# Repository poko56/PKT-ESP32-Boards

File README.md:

<h1 align="center">PKT ESP32 Boards</h1>

<p align="center">
  ชุดบอร์ด ESP32 ของ <b>POKOTEAM</b> ออกแบบด้วย KiCad 10 และสร้างจากสคริปต์ทั้งหมด
</p>

---

## บอร์ดทั้งหมด

### PKT ESP32-C3 Mini

บอร์ดไร้สายขนาดจิ๋ว 20 × 34 มม. เหมาะกับโหนด ESP-NOW, เซนเซอร์ไร้สาย และอุปกรณ์ในกล่องเล็ก
มี USB-C ในตัว ไฟเลี้ยงเป็น LDO ล้วน และมีโลโก้ PKT ด้านหลัง

- โมดูล ESP32-C3-MINI-1
- อุปกรณ์ SMD ด้านเดียว สั่ง PCBA ผ่าน JLCPCB ได้
- **สถานะ:** ไฟล์พร้อมสั่ง

[ดูรายละเอียดและวงจร](boards/c3-mini)

<br clear="right">

### ESP32 Dev Board

บอร์ดพัฒนาขนาด 29 × 54.6 มม. สำหรับเรียนรู้และทำต้นแบบบน breadboard
เสียบ USB-C แล้วอัปโหลดโค้ดได้เลย

- โมดูล ESP32-WROOM-32E
- CH340C พร้อมวงจร auto-reset
- **สถานะ:** มี Gerber

[ดูรายละเอียดและวงจร](boards/esp32-devboard)

<br clear="right">

### Robot Arm Controller

บอร์ดควบคุมแขนกล 5 แกน ขนาด 80 × 64 มม. สำหรับ SG90/MG90S ใช้ adapter 12V
แยกไฟ servo กับ logic มี E-stop และวัดกระแสได้

- PCA9685 + 74AHCT541 + TPS54560B + INA219
- พอร์ต DIO, ADC, I2C และ UART
- **สถานะ:** วงจรเสร็จ เดินลายยังไม่เสร็จ ยังสั่งผลิตไม่ได้

[ดูรายละเอียดและวงจร](boards/arm-controller)

<br clear="right">

> ยังไม่มีบอร์ดใดผ่านการทดสอบกับของจริง ตรวจด้วย ERC และ DRC ของ KiCad แล้วเท่านั้น

## โครงสร้าง repo

```text
PKT-ESP32-Boards
├── assets/                  โลโก้
└── boards/
    ├── c3-mini/             PKT ESP32-C3 Mini
    ├── esp32-devboard/      ESP32 Dev Board
    └── arm-controller/      Robot Arm Controller
```

แต่ละบอร์ดมีโครงสร้างเดียวกัน

| โฟลเดอร์ | เนื้อหา |
|---|---|
| `docs/` | ภาพวงจร ภาพบอร์ด และคำอธิบาย |
| `fab/` | Gerber, BOM, ตำแหน่งอุปกรณ์ และรายงาน ERC/DRC |
| `tools/` | สคริปต์สร้าง schematic และ PCB จาก `design.py` |

## Branch

| Branch | ใช้ทำอะไร |
|---|---|
| `main` | รวมทุกบอร์ด |
| `board/c3-mini` | งานของ ESP32-C3 Mini เท่านั้น |
| `board/esp32-devboard` | งานของ Dev Board เท่านั้น |
| `board/arm-controller` | งานของ Arm Controller เท่านั้น |

แก้บอร์ดไหนให้ทำใน branch ของบอร์ดนั้น แล้วค่อย merge เข้า `main`

## วิธีเปิดและสั่งผลิต

เปิดไฟล์ `.kicad_pro` ของบอร์ดใน KiCad 10

สั่ง C3 Mini ผ่าน JLCPCB ตามขั้นตอนใน [HOW_TO_ORDER.txt](boards/c3-mini/fab/HOW_TO_ORDER.txt)

แก้แบบจาก `tools/design.py` แล้วรัน `tools/build.sh` ในบอร์ดที่มีสคริปต์นี้ สคริปต์ใช้ KiCad บน macOS ที่ `/Applications/KiCad`

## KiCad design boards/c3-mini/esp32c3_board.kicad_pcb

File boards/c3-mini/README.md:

<h1 align="center">PKT ESP32-C3 Mini</h1>

<p align="center">บอร์ด ESP32-C3 ขนาด 20 × 34 มม. เน้นเล็ก ไฟสะอาด และสั่ง PCBA ผ่าน JLCPCB ได้</p>

## บอร์ดนี้คืออะไร

PKT ESP32-C3 Mini คือบอร์ดไร้สายขนาดจิ๋วที่มี USB-C ในตัว เสียบแล้วเขียนโปรแกรมได้เลย
ออกแบบมาสำหรับงานที่พื้นที่น้อยและต้องการการสื่อสารไร้สาย เช่น ESP-NOW, Wi-Fi และ Bluetooth LE

## เหมาะกับงานแบบไหน

- โหนดเซนเซอร์ไร้สาย
- อุปกรณ์สวมใส่หรืออุปกรณ์ในกล่องขนาดเล็ก
- รีโมตและตัวรับส่งข้อมูลระหว่างอุปกรณ์

## จุดเด่น

| หัวข้อ | รายละเอียด |
|---|---|
| USB | USB ในตัวชิป ไม่ต้องมีชิป USB-UART |
| ไฟเลี้ยง | LDO AP2112K-3.3 ไม่มีวงจรสวิตชิงบนบอร์ด |
| กรองไฟ | ferrite ที่ไฟเข้า และ C กรองไฟหลายค่า |
| ป้องกัน | USBLC6 กัน ESD และ B5819W กันไฟย้อน |
| เสาอากาศ | ไม่มีทองแดงในเขตเสาอากาศ |
| การประกอบ | อุปกรณ์ SMD อยู่ด้านเดียว |

## สเปก

| รายการ | ค่า |
|---|---|
| ขนาด | 20 × 34 มม. PCB 2 ชั้น |
| โมดูล | ESP32-C3-MINI-1 |
| ไฟเข้า | USB-C หรือขา 5V |
| ขา I/O | header 7 ขา 2 แถว ห่างกัน 15.24 มม. |
| GPIO | 0-7, 10, TX, RX |
| ปุ่มและไฟ | RST, BOOT, LED ที่ IO8 |

## วงจร

ดูแบบซูมได้ที่ [schematic.pdf](docs/schematic.pdf)

## สั่งผลิต

ไฟล์อยู่ใน [`fab/`](fab) และดูขั้นตอนได้ที่ [HOW_TO_ORDER.txt](fab/HOW_TO_ORDER.txt)

> สถานะ: DRC ไม่มี error และ ERC ผ่าน แต่ยังไม่ได้ทดสอบกับบอร์ดจริง
> รหัสอะไหล่บางตัวต้องยืนยันในหน้าจับคู่ของ JLCPCB ก่อนสั่ง

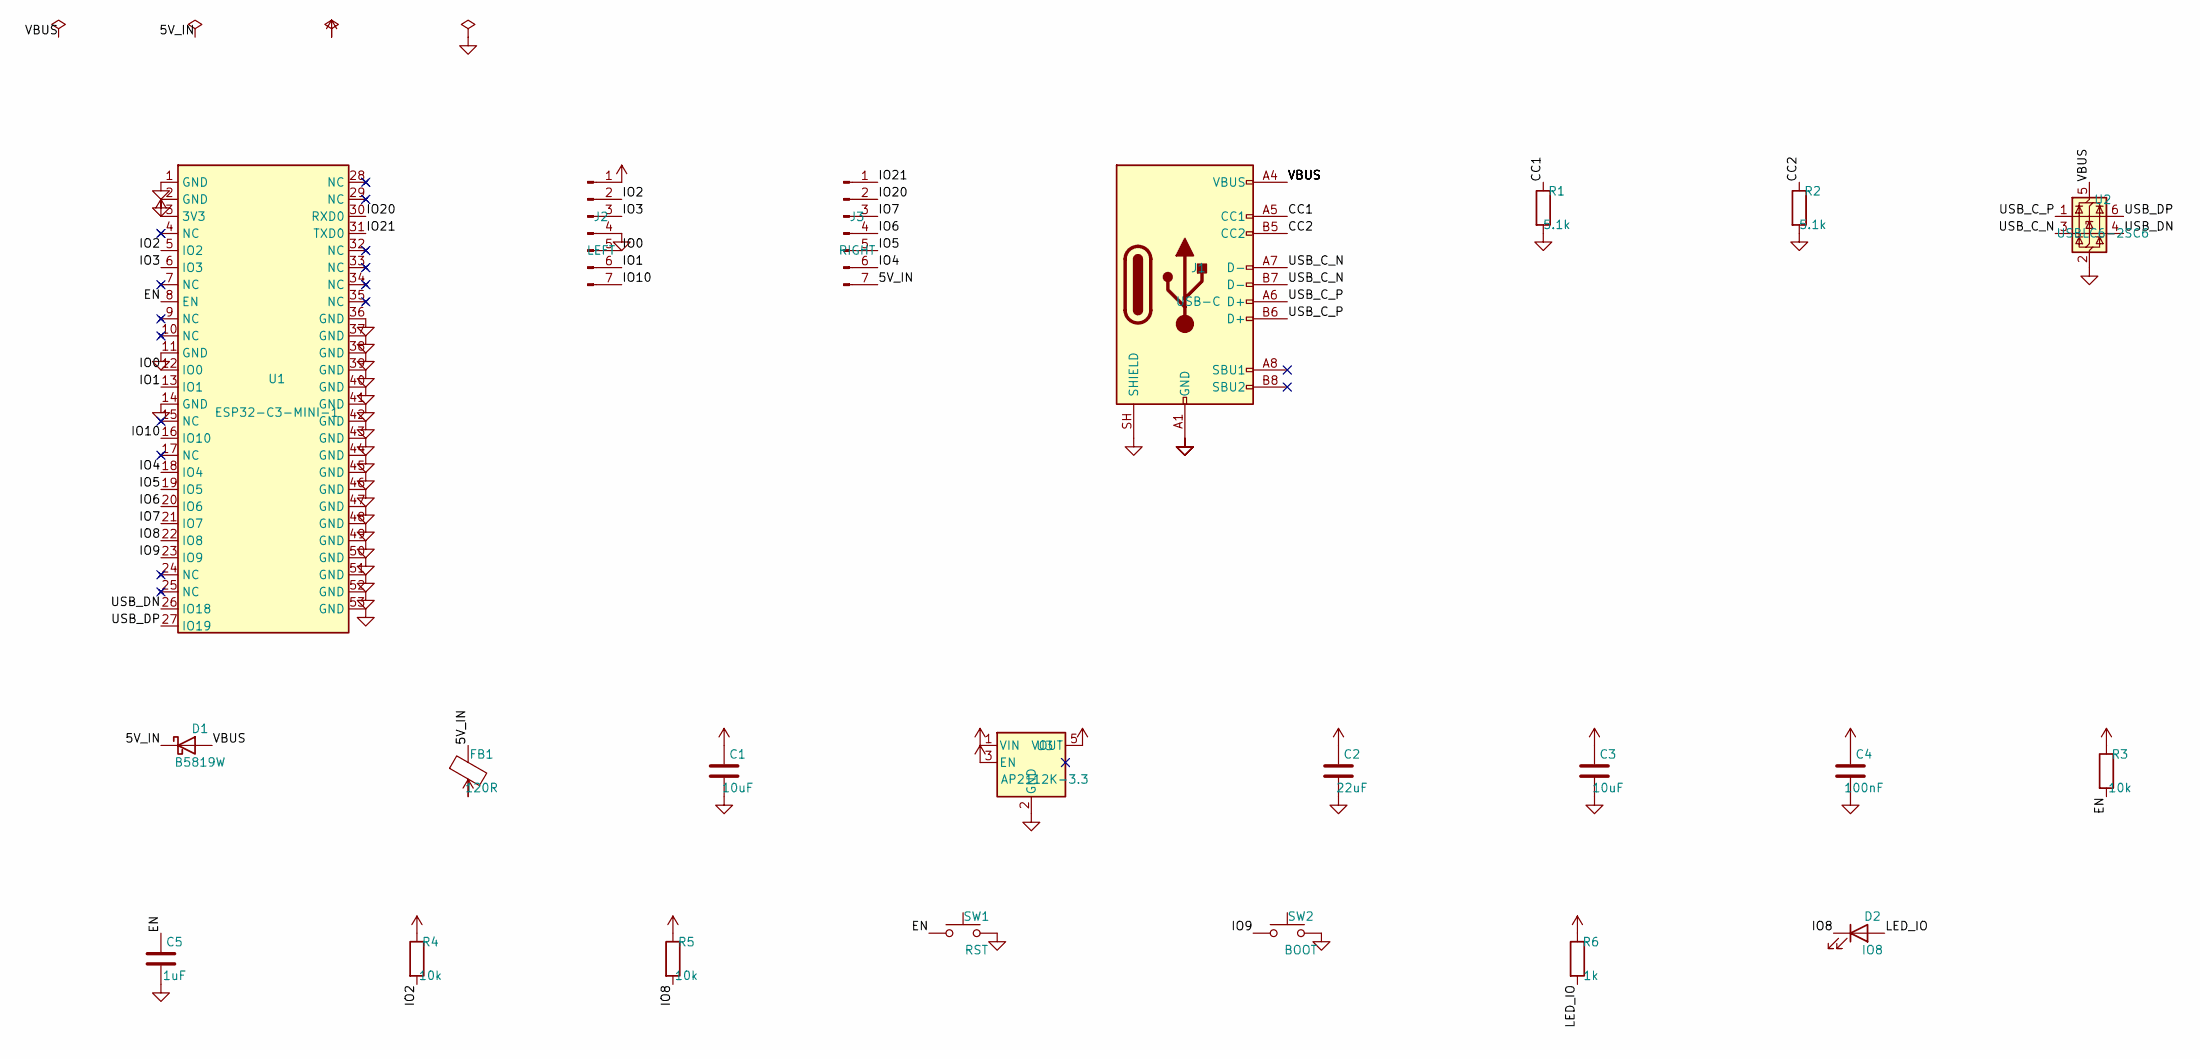
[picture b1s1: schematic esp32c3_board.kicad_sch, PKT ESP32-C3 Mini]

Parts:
C1, C3: 10uF; C_0603_1608Metric; MPN 10uF X5R/X7R 0603
C2: 22uF; C_0805_2012Metric; MPN 22uF X5R/X7R 0805
C4: 100nF; C_0402_1005Metric; MPN 100nF X5R/X7R 0402
C5: 1uF; C_0402_1005Metric; MPN 1uF X5R/X7R 0402
D1: B5819W; D_SOD-123; MPN B5819W
D2: IO8; LED_0603_1608Metric; MPN LED 0603 blue
FB1: 120R; L_0603_1608Metric; MPN 120R@100MHz >=1A 0603
J1: USB-C; USB_C_Receptacle_HRO_TYPE-C-31-M-12; MPN HRO TYPE-C-31-M-12
J2: LEFT; PinHeader_1x07_P2.54mm_Vertical; MPN 2.54mm 1x7 header (not assembled)
J3: RIGHT; PinHeader_1x07_P2.54mm_Vertical; MPN 2.54mm 1x7 header (not assembled)
R1, R2: 5.1k; R_0402_1005Metric; MPN 5.1k 1% 0402
R3, R4, R5: 10k; R_0402_1005Metric; MPN 10k 1% 0402
R6: 1k; R_0402_1005Metric; MPN 1k 1% 0402
SW1: RST; SW_Push_1P1T_NO_CK_KMR2; MPN SMD tact 4.2x2.8mm
SW2: BOOT; SW_Push_1P1T_NO_CK_KMR2; MPN SMD tact 4.2x2.8mm
U1: ESP32-C3-MINI-1; ESP32-C6-MINI-1; MPN ESP32-C3-MINI-1-N4
U2: USBLC6-2SC6; SOT-23-6; MPN USBLC6-2SC6
U3: AP2112K-3.3; SOT-23-5; MPN AP2112K-3.3TRG1

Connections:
+3V3: C2.1, C3.1, C4.1, J2.1, R3.1, R4.1, R5.1, R6.1, U1.3 (3V3), U3.5 (VOUT)
+5V: C1.1, FB1.2, U3.1 (VIN), U3.3 (EN)
/5V_IN: D1.1 (K), FB1.1, J3.7
/CC1: J1.A5 (CC1), R1.1
/CC2: J1.B5 (CC2), R2.1
/EN: C5.1, R3.2, SW1.1, U1.8 (EN)
/IO0: J2.5, U1.12 (IO0)
/IO1: J2.6, U1.13 (IO1)
/IO2: J2.2, R4.2, U1.5 (IO2)
/IO3: J2.3, U1.6 (IO3)
/IO4: J3.6, U1.18 (IO4)
/IO5: J3.5, U1.19 (IO5)
/IO6: J3.4, U1.20 (IO6)
/IO7: J3.3, U1.21 (IO7)
/IO8: D2.1 (K), R5.2, U1.22 (IO8)
/IO9: SW2.1, U1.23 (IO9)
/IO10: J2.7, U1.16 (IO10)
/IO20: J3.2, U1.30 (RXD0)
/IO21: J3.1, U1.31 (TXD0)
/LED_IO: D2.2 (A), R6.2
/USB_C_N: J1.A7 (D-), J1.B7 (D-), U2.3 (I/O2)
/USB_C_P: J1.A6 (D+), J1.B6 (D+), U2.1 (I/O1)
/USB_DN: U1.26 (IO18), U2.4 (I/O2)
/USB_DP: U1.27 (IO19), U2.6 (I/O1)
/VBUS: D1.2 (A), J1.A4 (VBUS), J1.A9 (VBUS), J1.B4 (VBUS), J1.B9 (VBUS), U2.5 (VBUS)
GND: C1.2, C2.2, C3.2, C4.2, C5.2, J1.A1 (GND), J1.A12 (GND), J1.B1 (GND), J1.B12 (GND), J1.SH (SHIELD), J2.4, R1.2, R2.2, SW1.2, SW2.2, U1.1 (GND), U1.2 (GND), U1.11 (GND), U1.14 (GND), U1.36 (GND), U1.37 (GND), U1.38 (GND), U1.39 (GND), U1.40 (GND), U1.41 (GND), U1.42 (GND), U1.43 (GND), U1.44 (GND), U1.45 (GND), U1.46 (GND), U1.47 (GND), U1.48 (GND), U1.49 (GND), U1.50 (GND), U1.51 (GND), U1.52 (GND), U1.53 (GND), U2.2 (GND), U3.2 (GND)

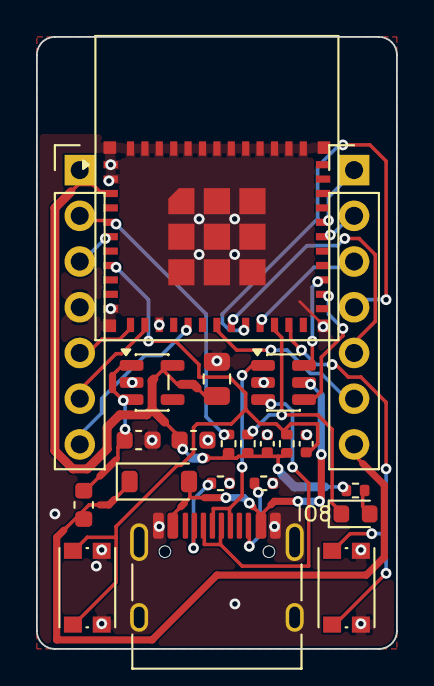
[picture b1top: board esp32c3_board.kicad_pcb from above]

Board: 2 copper layers, 20.0 x 34.0 mm, 22 parts (0 on the bottom side), 26 nets.

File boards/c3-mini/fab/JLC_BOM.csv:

Comment,Designator,Footprint,LCSC Part #,Check
10uF X5R/X7R 0603,"C1,C3",C_0603_1608Metric,C19702,confirm in JLC
22uF X5R/X7R 0805,C2,C_0805_2012Metric,C45783,confirm in JLC
100nF X5R/X7R 0402,C4,C_0402_1005Metric,C1525,confirm in JLC
1uF X5R/X7R 0402,C5,C_0402_1005Metric,C52923,confirm in JLC
B5819W,D1,D_SOD-123,C8598,verified
LED 0603 blue,D2,LED_0603_1608Metric,,pick part in JLC
120R@100MHz >=1A 0603,FB1,L_0603_1608Metric,,pick part in JLC
HRO TYPE-C-31-M-12,J1,USB_C_Receptacle_HRO_TYPE-C-31-M-12,C165948,confirm in JLC
5.1k 1% 0402,"R1,R2",R_0402_1005Metric,C25905,confirm in JLC
10k 1% 0402,"R3,R4,R5",R_0402_1005Metric,C25744,confirm in JLC
1k 1% 0402,R6,R_0402_1005Metric,C11702,confirm in JLC
SMD tact 4.2x2.8mm,"SW1,SW2",SW_Push_1P1T_NO_CK_KMR2,,pick part in JLC
ESP32-C3-MINI-1-N4,U1,ESP32-C6-MINI-1,C2838502,verified
USBLC6-2SC6,U2,SOT-23-6,C7519,confirm in JLC
AP2112K-3.3TRG1,U3,SOT-23-5,C51118,verified

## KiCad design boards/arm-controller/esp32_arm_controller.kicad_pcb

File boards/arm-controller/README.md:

<h1 align="center">PKT ESP32 Robot Arm Controller</h1>

<p align="center">บอร์ดควบคุมแขนกล 5 แกนสำหรับ SG90/MG90S ขนาด 80 × 64 มม. ใช้ adapter 12V</p>

> **ยังสั่งผลิตไม่ได้** วงจรเสร็จแล้ว แต่การเดินลายยังไม่สำเร็จ ภาพด้านบนคือการวางอุปกรณ์

## บอร์ดนี้คืออะไร

บอร์ดควบคุมแขนกลที่แยกไฟ servo ออกจากไฟของ ESP32 เพื่อไม่ให้บอร์ดรีเซ็ตเมื่อ servo กระชากไฟ
มีปุ่มหยุดฉุกเฉิน และจ่ายไฟ servo ก็ต่อเมื่อ firmware สั่งเปิด

## เหมาะกับงานแบบไหน

- แขนกลตั้งโต๊ะ 5 แกน
- งานหยิบวางและโครงงานหุ่นยนต์
- ระบบที่ต้องอ่าน limit switch และตำแหน่งจากโพเทนชิออมิเตอร์

## จุดเด่น

| หัวข้อ | รายละเอียด |
|---|---|
| PWM | PCA9685 สร้างสัญญาณแยกจาก CPU |
| สัญญาณ servo | บัฟเฟอร์ 74AHCT541 ระดับ 5V |
| ไฟ servo | บัค TPS54560B 5V ค่าอิงจาก datasheet ของ TI |
| ไฟ logic | บัค AP63205 แยกต่างหาก มีไดโอดและ C hold-up |
| ความปลอดภัย | E-stop แบบ fail-safe และบูตมา servo จะดับ |
| วัดผล | INA219 วัดกระแสและแรงดันราง servo |

## พอร์ต

| พอร์ต | จำนวน |
|---|---|
| Servo (S + -) | 5 |
| DIO พร้อมตัวกรอง | 5 |
| ADC พร้อมตัวกรอง | 4 |
| I2C | 2 |
| UART | 1 |
| ESTOP | 1 |

ต้องต่อสวิตช์ NC หรือจั๊มเปอร์ที่ ESTOP ไม่เช่นนั้น servo จะไม่ได้ไฟ

## วงจร

ดูแบบซูมได้ที่ [schematic.pdf](docs/schematic.pdf) และดูประมาณราคาอุปกรณ์ได้ที่ [bom_with_prices.csv](bom_with_prices.csv)

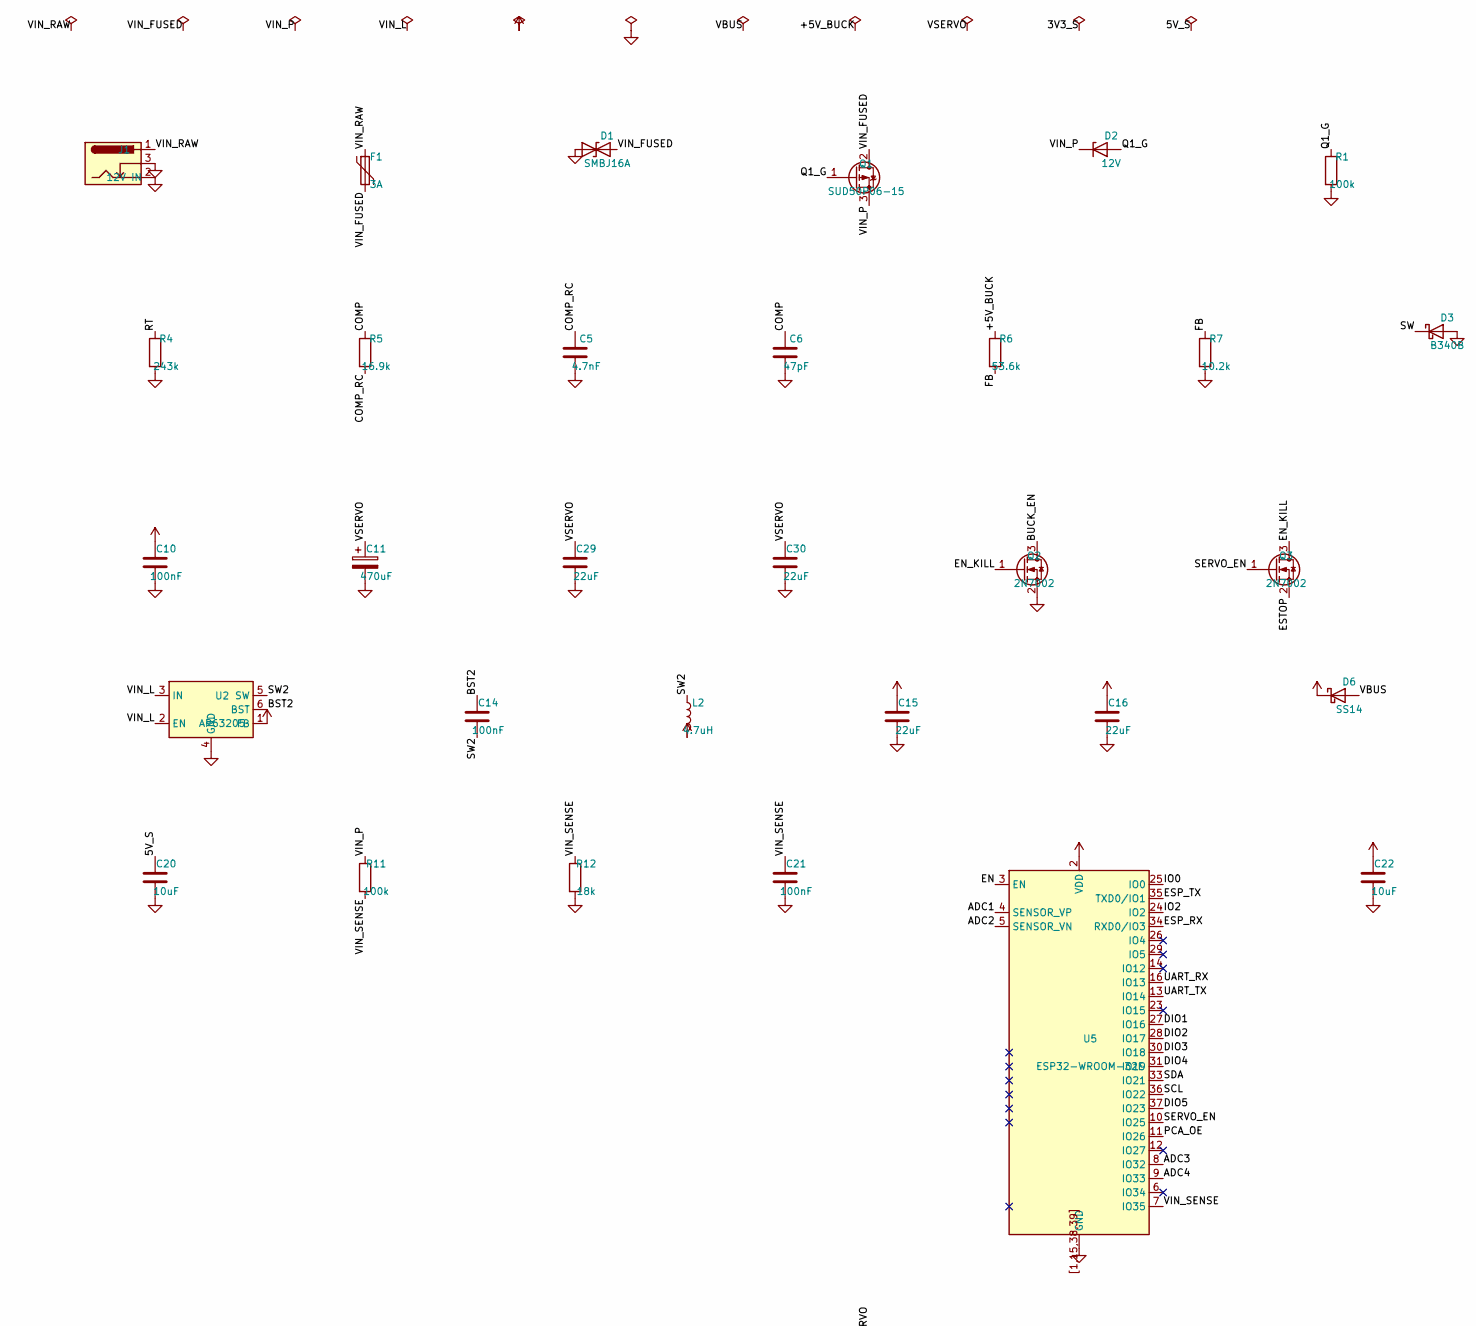
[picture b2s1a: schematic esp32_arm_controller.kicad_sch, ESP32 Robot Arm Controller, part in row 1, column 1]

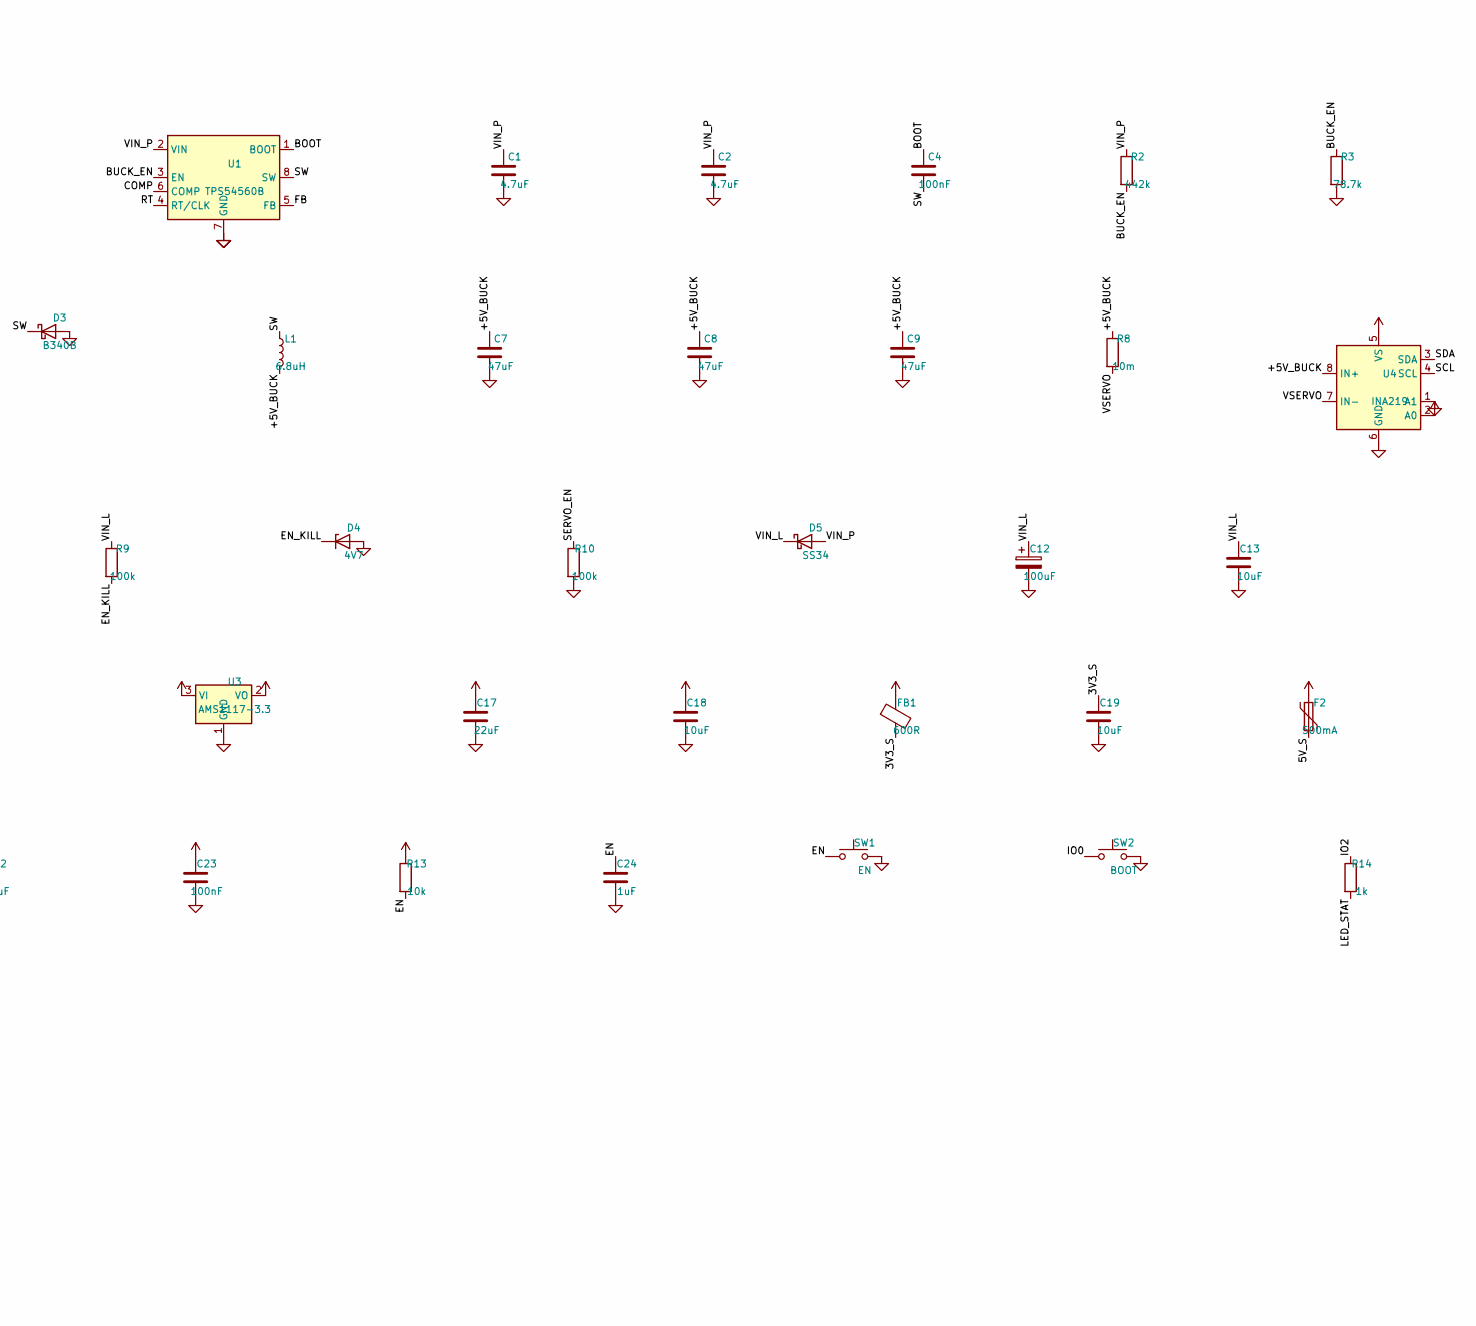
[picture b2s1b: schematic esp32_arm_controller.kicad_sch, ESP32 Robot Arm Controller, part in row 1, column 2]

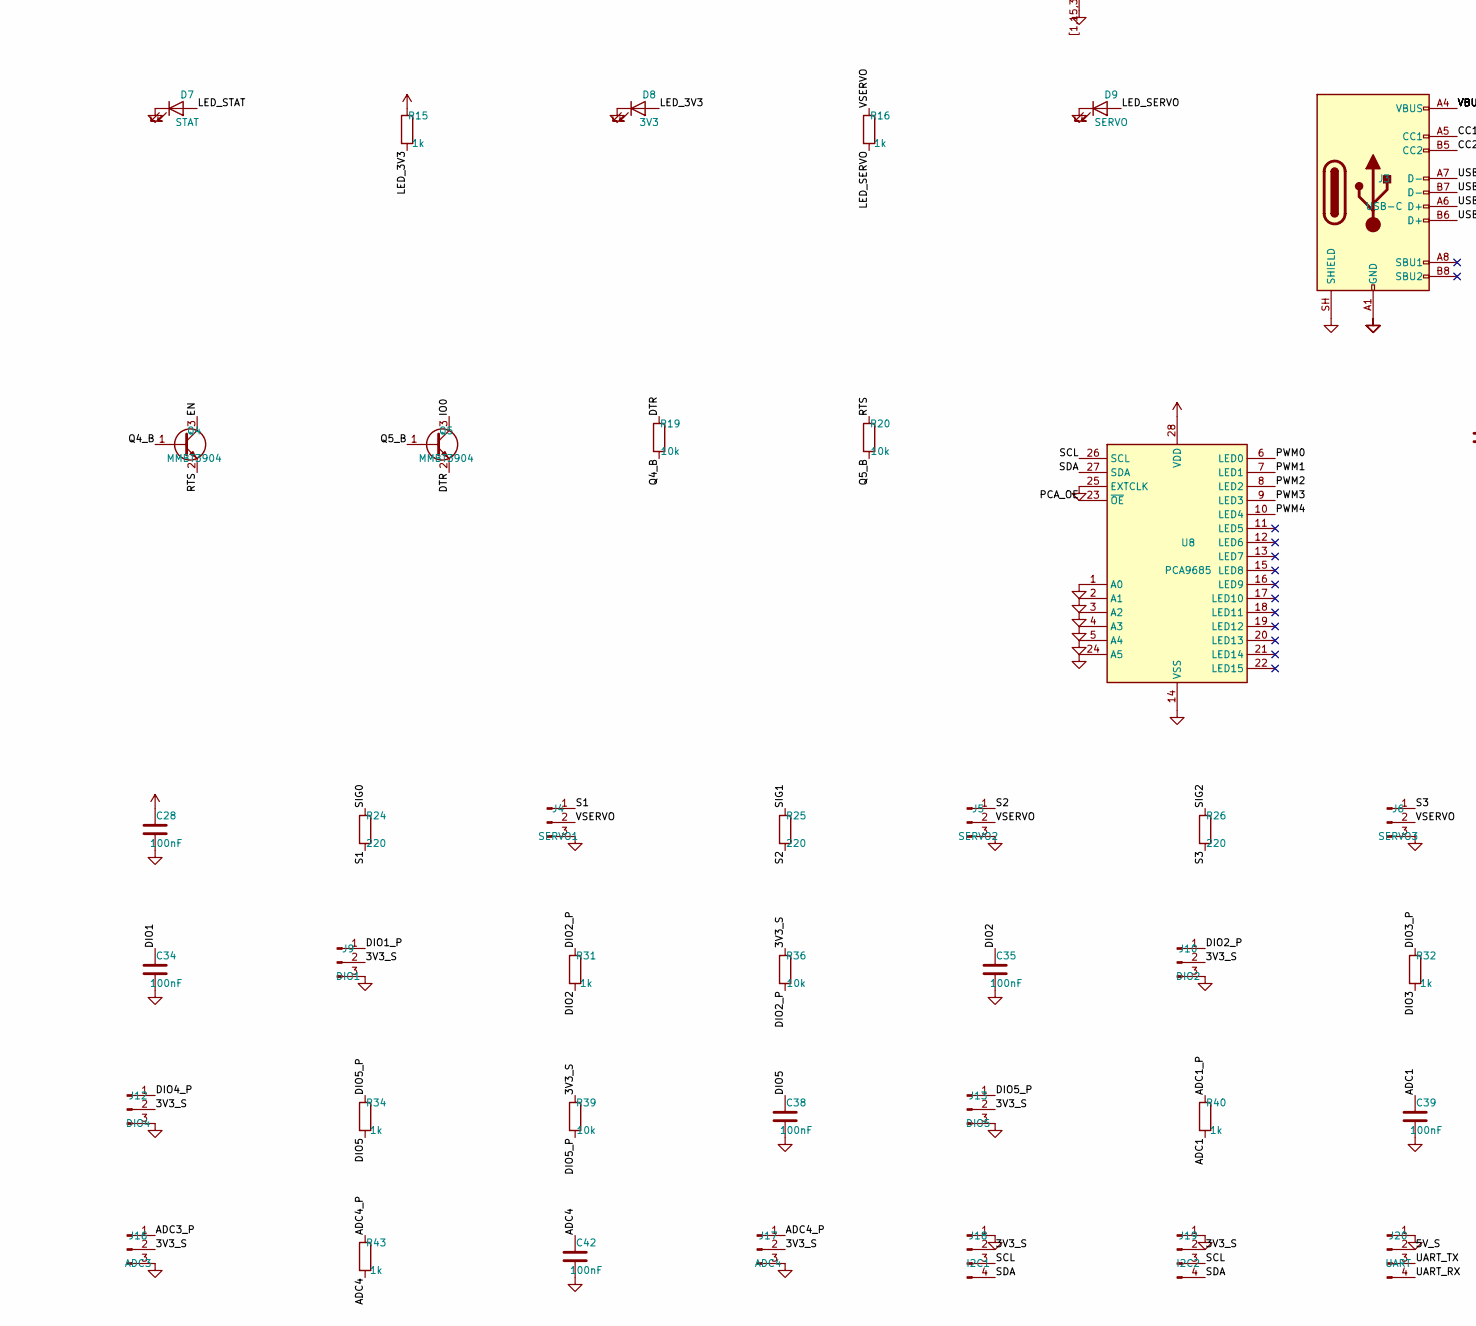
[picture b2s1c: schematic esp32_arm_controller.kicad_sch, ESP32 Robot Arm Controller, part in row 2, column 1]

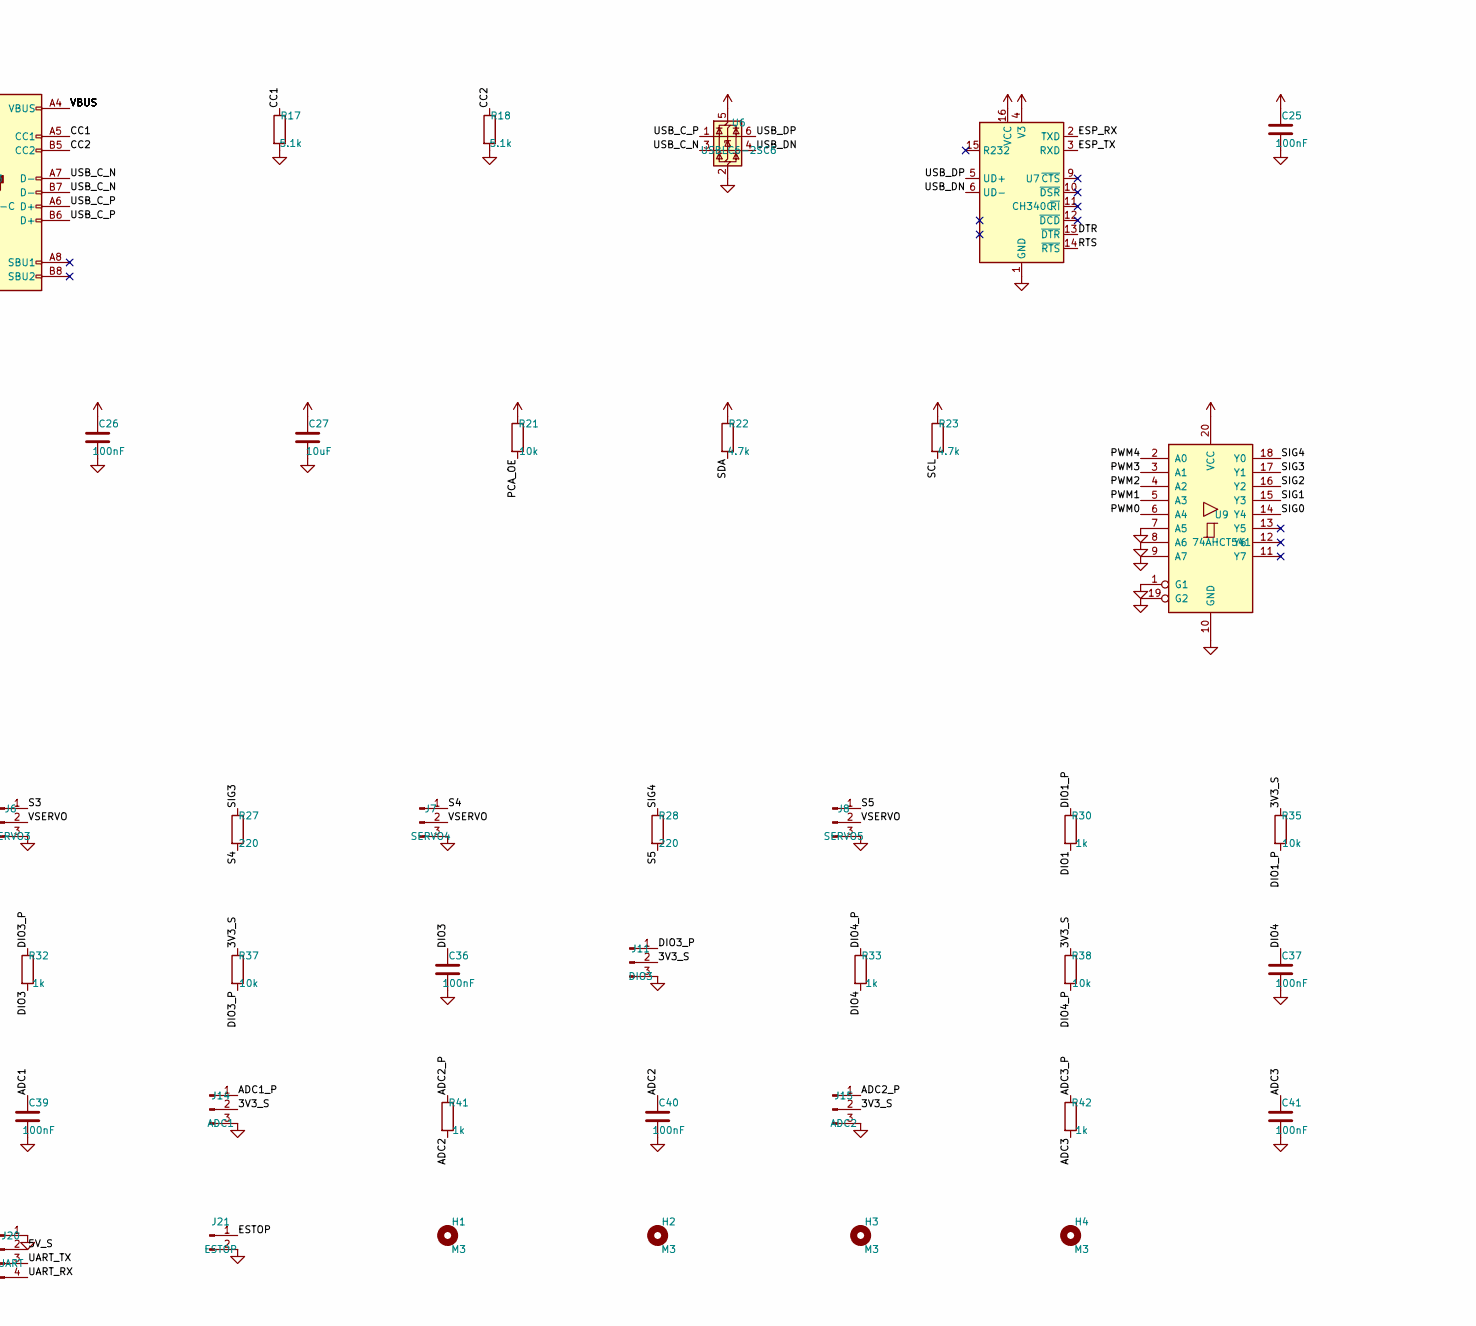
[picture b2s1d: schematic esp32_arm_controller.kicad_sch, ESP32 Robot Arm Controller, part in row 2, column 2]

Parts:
C1, C2: 4.7uF; C_1210_3225Metric; MPN 4.7uF 50V X7R 1210
C4: 100nF; C_0603_1608Metric; MPN 100nF 16V X7R 0603
C5: 4.7nF; C_0603_1608Metric; MPN 4.7nF X7R _060
C6: 47pF; C_0603_1608Metric; MPN 47pF X7R _060
C7, C8, C9: 47uF; C_1210_3225Metric; MPN 47uF 10V X5R 1210
C10, C14, C21, C23, C25, C26, C28, C34, C35, C36, C37, C38, C39, C40, C41, C42: 100nF; C_0603_1608Metric; MPN 100nF X7R _060
C11: 470uF; CP_Radial_D8.0mm_P3.50mm; MPN 470uF 10V low-ESR D8
C12: 100uF; CP_Elec_6.3x7.7; MPN 100uF 25V
C13: 10uF; C_1206_3216Metric; MPN 10uF 25V X7R 1206
C15, C16, C17, C29, C30: 22uF; C_0805_2012Metric; MPN 22uF 10V X5R 0805
C18, C19, C20, C22, C27: 10uF; C_0805_2012Metric; MPN 10uF 10V X5R 0805
C24: 1uF; C_0603_1608Metric; MPN 1uF X7R _060
D1: SMBJ16A; D_SMB; MPN SMBJ16A
D2: 12V; D_SOD-123; MPN BZT52C12 12V zener
D3: B340B; D_SMB; MPN B340B 40V 3A
D4: 4V7; D_SOD-123; MPN BZT52C4V7 zener
D5: SS34; D_SMA; MPN SS34
D6: SS14; D_SMA; MPN SS14
D7: STAT; LED_0603_1608Metric; MPN LED 0603 blue
D8: 3V3; LED_0603_1608Metric; MPN LED 0603 green
D9: SERVO; LED_0603_1608Metric; MPN LED 0603 red
F1: 3A; Fuse_1812_4532Metric; MPN PTC 1812 hold 3A, >=16V
F2: 500mA; Fuse_1206_3216Metric; MPN PTC 1206 hold 500mA
FB1: 600R; L_0805_2012Metric; MPN 600R@100MHz 0805
H1, H2, H3, H4: M3; MountingHole_3.2mm_M3; MPN M3 hole
J1: 12V IN; BarrelJack_CUI_PJ-063AH_Horizontal; MPN CUI PJ-063AH
J3: USB-C; USB_C_Receptacle_HRO_TYPE-C-31-M-12; MPN HRO TYPE-C-31-M-12
J4: SERVO1; PinHeader_1x03_P2.54mm_Vertical; MPN 2.54mm 1x3 header
J5: SERVO2; PinHeader_1x03_P2.54mm_Vertical; MPN 2.54mm 1x3 header
J6: SERVO3; PinHeader_1x03_P2.54mm_Vertical; MPN 2.54mm 1x3 header
J7: SERVO4; PinHeader_1x03_P2.54mm_Vertical; MPN 2.54mm 1x3 header
J8: SERVO5; PinHeader_1x03_P2.54mm_Vertical; MPN 2.54mm 1x3 header
J9: DIO1; PinHeader_1x03_P2.54mm_Vertical; MPN 2.54mm 1x3 header
J10: DIO2; PinHeader_1x03_P2.54mm_Vertical; MPN 2.54mm 1x3 header
J11: DIO3; PinHeader_1x03_P2.54mm_Vertical; MPN 2.54mm 1x3 header
J12: DIO4; PinHeader_1x03_P2.54mm_Vertical; MPN 2.54mm 1x3 header
J13: DIO5; PinHeader_1x03_P2.54mm_Vertical; MPN 2.54mm 1x3 header
J14: ADC1; PinHeader_1x03_P2.54mm_Vertical; MPN 2.54mm 1x3 header
J15: ADC2; PinHeader_1x03_P2.54mm_Vertical; MPN 2.54mm 1x3 header
J16: ADC3; PinHeader_1x03_P2.54mm_Vertical; MPN 2.54mm 1x3 header
J17: ADC4; PinHeader_1x03_P2.54mm_Vertical; MPN 2.54mm 1x3 header
J18: I2C1; PinHeader_1x04_P2.54mm_Vertical; MPN 2.54mm 1x4 header
J19: I2C2; PinHeader_1x04_P2.54mm_Vertical; MPN 2.54mm 1x4 header
J20: UART; PinHeader_1x04_P2.54mm_Vertical; MPN 2.54mm 1x4 header
J21: ESTOP; PinHeader_1x02_P2.54mm_Vertical; MPN 2.54mm 1x2 header
L1: 6.8uH; L_Bourns-SRN8040_8x8.15mm; MPN 6.8uH Isat>=5A 8x8mm
L2: 4.7uH; L_Bourns-SRN4018; MPN 4.7uH Isat>=3A 4x4mm
Q1: SUD50P06-15; TO-252-2; MPN SUD50P06-15
Q2, Q3: 2N7002; SOT-23; MPN 2N7002
Q4, Q5: MMBT3904; SOT-23; MPN MMBT3904
R1, R9, R10, R11: 100k; R_0603_1608Metric; MPN 100k 1% 0603
R2: 442k; R_0603_1608Metric; MPN 442k 1% 0603
R3: 78.7k; R_0603_1608Metric; MPN 78.7k 1% 0603
R4: 243k; R_0603_1608Metric; MPN 243k 1% 0603
R5: 16.9k; R_0603_1608Metric; MPN 16.9k 1% 0603
R6: 53.6k; R_0603_1608Metric; MPN 53.6k 1% 0603
R7: 10.2k; R_0603_1608Metric; MPN 10.2k 1% 0603
R8: 10m; R_2512_6332Metric; MPN 10mR 1% 2W 2512
R12: 18k; R_0603_1608Metric; MPN 18k 1% 0603
R13, R19, R20, R21, R35, R36, R37, R38, R39: 10k; R_0603_1608Metric; MPN 10k 1% 0603
R14, R15, R16, R30, R31, R32, R33, R34, R40, R41, R42, R43: 1k; R_0603_1608Metric; MPN 1k 1% 0603
R17, R18: 5.1k; R_0603_1608Metric; MPN 5.1k 1% 0603
R22, R23: 4.7k; R_0603_1608Metric; MPN 4.7k 1% 0603
R24, R25, R26, R27, R28: 220; R_0603_1608Metric; MPN 220 1% 0603
SW1: EN; SW_Push_1P1T_NO_CK_KMR2; MPN CK KMR2
SW2: BOOT; SW_Push_1P1T_NO_CK_KMR2; MPN CK KMR2
U1: TPS54560B; Texas_R-PDSO-G8_EP2.95x4.9mm_Mask2.4x3.1mm_ThermalVias; MPN TPS54560BDDAR
U2: AP63205; TSOT-23-6; MPN AP63205WU-7
U3: AMS1117-3.3; SOT-223-3_TabPin2; MPN AMS1117-3.3
U4: INA219; SOIC-8_3.9x4.9mm_P1.27mm; MPN INA219AIDR
U5: ESP32-WROOM-32E; MPN ESP32-WROOM-32E-N4
U6: USBLC6-2SC6; SOT-23-6; MPN USBLC6-2SC6
U7: CH340C; SOIC-16_3.9x9.9mm_P1.27mm; MPN CH340C
U8: PCA9685; TSSOP-28_4.4x9.7mm_P0.65mm; MPN PCA9685PW
U9: 74AHCT541; TSSOP-20_4.4x6.5mm_P0.65mm; MPN SN74AHCT541PWR

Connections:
+3V3: C10.1, C17.1, C18.1, C22.1, C23.1, C25.1, C26.1, C27.1, FB1.1, R13.1, R15.1, R21.1, R22.1, R23.1, U3.2 (VO), U4.2 (A0), U4.5 (VS), U5.2 (VDD), U7.4 (V3), U7.16 (VCC), U8.28 (VDD)
+5V: C15.1, C16.1, C28.1, D6.1 (K), F2.1, L2.2, U2.1 (FB), U3.3 (VI), U6.5 (VBUS), U9.20 (VCC)
/3V3_S: C19.1, FB1.2, J9.2, J10.2, J11.2, J12.2, J13.2, J14.2, J15.2, J16.2, J17.2, J18.2, J19.2, R35.1, R36.1, R37.1, R38.1, R39.1
/5V_S: C20.1, F2.2, J20.2
/+5V_BUCK: C7.1, C8.1, C9.1, L1.2, R6.1, R8.1, U4.8 (IN+)
/ADC1: C39.1, R40.2, U5.4 (SENSOR_VP)
/ADC1_P: J14.1, R40.1
/ADC2: C40.1, R41.2, U5.5 (SENSOR_VN)
/ADC2_P: J15.1, R41.1
/ADC3: C41.1, R42.2, U5.8 (IO32)
/ADC3_P: J16.1, R42.1
/ADC4: C42.1, R43.2, U5.9 (IO33)
/ADC4_P: J17.1, R43.1
/BOOT: C4.1, U1.1 (BOOT)
/BST2: C14.1, U2.6 (BST)
/BUCK_EN: Q2.3 (D), R2.2, R3.1, U1.3 (EN)
/CC1: J3.A5 (CC1), R17.1
/CC2: J3.B5 (CC2), R18.1
/COMP: C6.1, R5.1, U1.6 (COMP)
/COMP_RC: C5.1, R5.2
/DIO1: C34.1, R30.2, U5.27 (IO16)
/DIO1_P: J9.1, R30.1, R35.2
/DIO2: C35.1, R31.2, U5.28 (IO17)
/DIO2_P: J10.1, R31.1, R36.2
/DIO3: C36.1, R32.2, U5.30 (IO18)
/DIO3_P: J11.1, R32.1, R37.2
/DIO4: C37.1, R33.2, U5.31 (IO19)
/DIO4_P: J12.1, R33.1, R38.2
/DIO5: C38.1, R34.2, U5.37 (IO23)
/DIO5_P: J13.1, R34.1, R39.2
/DTR: Q5.2 (E), R19.1, U7.13 (~DTR)
/EN: C24.1, Q4.3 (C), R13.2, SW1.1, U5.3 (EN)
/EN_KILL: D4.1 (K), Q2.1 (G), Q3.3 (D), R9.2
/ESP_RX: U5.34 (RXD0/IO3), U7.2 (TXD)
/ESP_TX: U5.35 (TXD0/IO1), U7.3 (RXD)
/ESTOP: J21.1, Q3.2 (S)
/FB: R6.2, R7.1, U1.5 (FB)
/IO0: Q5.3 (C), SW2.1, U5.25 (IO0)
/IO2: R14.1, U5.24 (IO2)
/LED_3V3: D8.2 (A), R15.2
/LED_SERVO: D9.2 (A), R16.2
/LED_STAT: D7.2 (A), R14.2
/PCA_OE: R21.2, U5.11 (IO26), U8.23 (~OE)
/PWM0: U8.6 (LED0), U9.6 (A4)
/PWM1: U8.7 (LED1), U9.5 (A3)
/PWM2: U8.8 (LED2), U9.4 (A2)
/PWM3: U8.9 (LED3), U9.3 (A1)
/PWM4: U8.10 (LED4), U9.2 (A0)
/Q1_G: D2.2 (A), Q1.1 (G), R1.1
/Q4_B: Q4.1 (B), R19.2
/Q5_B: Q5.1 (B), R20.2
/RT: R4.1, U1.4 (RT/CLK)
/RTS: Q4.2 (E), R20.1, U7.14 (~RTS)
/S1: J4.1, R24.2
/S2: J5.1, R25.2
/S3: J6.1, R26.2
/S4: J7.1, R27.2
/S5: J8.1, R28.2
/SCL: J18.3, J19.3, R23.2, U4.4 (SCL), U5.36 (IO22), U8.26 (SCL)
/SDA: J18.4, J19.4, R22.2, U4.3 (SDA), U5.33 (IO21), U8.27 (SDA)
/SERVO_EN: Q3.1 (G), R10.1, U5.10 (IO25)
/SIG0: R24.1, U9.14 (Y4)
/SIG1: R25.1, U9.15 (Y3)
/SIG2: R26.1, U9.16 (Y2)
/SIG3: R27.1, U9.17 (Y1)
/SIG4: R28.1, U9.18 (Y0)
/SW: C4.2, D3.1 (K), L1.1, U1.8 (SW)
/SW2: C14.2, L2.1, U2.5 (SW)
/UART_RX: J20.4, U5.16 (IO13)
/UART_TX: J20.3, U5.13 (IO14)
/USB_C_N: J3.A7 (D-), J3.B7 (D-), U6.3 (I/O2)
/USB_C_P: J3.A6 (D+), J3.B6 (D+), U6.1 (I/O1)
/USB_DN: U6.4 (I/O2), U7.6 (UD-)
/USB_DP: U6.6 (I/O1), U7.5 (UD+)
/VBUS: D6.2 (A), J3.A4 (VBUS), J3.A9 (VBUS), J3.B4 (VBUS), J3.B9 (VBUS)
/VIN_FUSED: D1.2 (A2), F1.2, Q1.2 (D)
/VIN_L: C12.1, C13.1, D5.1 (K), R9.1, U2.2 (EN), U2.3 (IN)
/VIN_P: C1.1, C2.1, D2.1 (K), D5.2 (A), Q1.3 (S), R2.1, R11.1, U1.2 (VIN)
/VIN_RAW: F1.1, J1.1
/VIN_SENSE: C21.1, R11.2, R12.1, U5.7 (IO35)
/VSERVO: C11.1, C29.1, C30.1, J4.2, J5.2, J6.2, J7.2, J8.2, R8.2, R16.1, U4.7 (IN-)
GND: C1.2, C2.2, C5.2, C6.2, C7.2, C8.2, C9.2, C10.2, C11.2, C12.2, C13.2, C15.2, C16.2, C17.2, C18.2, C19.2, C20.2, C21.2, C22.2, C23.2, C24.2, C25.2, C26.2, C27.2, C28.2, C29.2, C30.2, C34.2, C35.2, C36.2, C37.2, C38.2, C39.2, C40.2, C41.2, C42.2, D1.1 (A1), D3.2 (A), D4.2 (A), D7.1 (K), D8.1 (K), D9.1 (K), J1.2, J1.3, J3.A1 (GND), J3.A12 (GND), J3.B1 (GND), J3.B12 (GND), J3.SH (SHIELD), J4.3, J5.3, J6.3, J7.3, J8.3, J9.3, J10.3, J11.3, J12.3, J13.3, J14.3, J15.3, J16.3, J17.3, J18.1, J19.1, J20.1, J21.2, Q2.2 (S), R1.2, R3.2, R4.2, R7.2, R10.2, R12.2, R17.2, R18.2, SW1.2, SW2.2, U1.7 (GND), U1.9 (GND)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

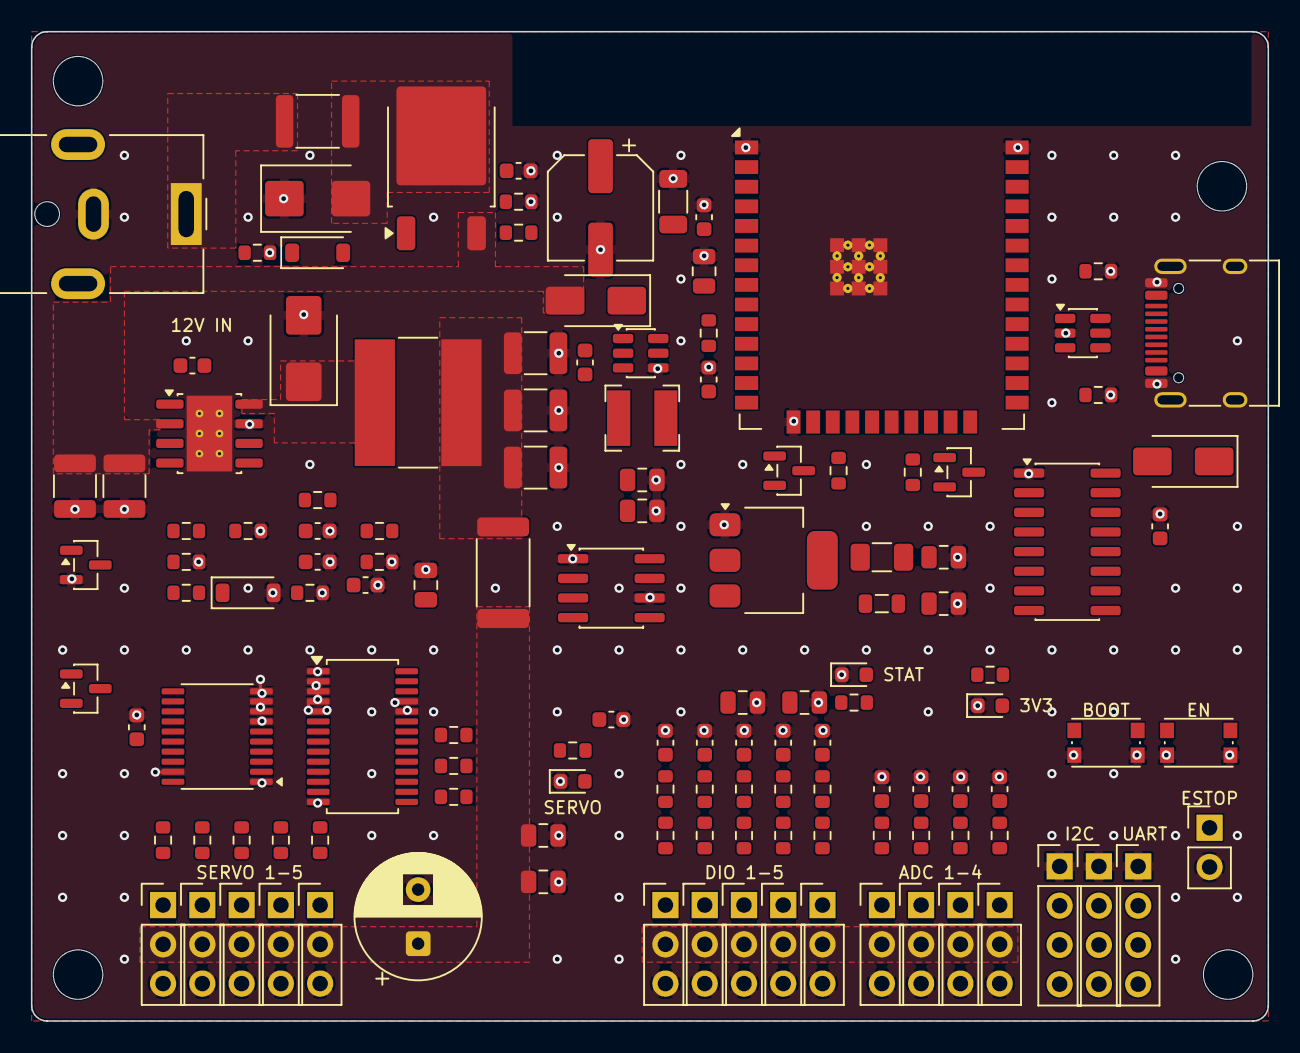
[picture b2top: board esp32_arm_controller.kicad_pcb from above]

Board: 2 copper layers, 80.0 x 64.0 mm, 134 parts (0 on the bottom side), 82 nets.

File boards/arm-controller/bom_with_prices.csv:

จำนวน,ตำแหน่ง,รายการ,Footprint,ราคาต่อชิ้น (USD),รวม (USD),รวม (บาท @33),ที่มาราคา
1,U8,PCA9685PW,TSSOP-28_4.4x9.7mm_P0.65mm,4.030,4.03,132.99,ค้นจากเว็บ
1,U5,ESP32-WROOM-32E-N4,ESP32-WROOM-32E,3.750,3.75,123.75,ค้นจากเว็บ
1,U1,TPS54560BDDAR,Texas_R-PDSO-G8_EP2.95x4.9mm_Mask2.4x3.1mm_ThermalVias,1.990,1.99,65.67,ค้นจากเว็บ
1,Q1,SUD50P06-15,TO-252-2,1.500,1.50,49.50,ประมาณการ
3,C7 C8 C9,47uF 10V X5R 1210,C_1210_3225Metric,0.400,1.20,39.60,ประมาณการ
14,J4 J5 J6 J7 J8 J9 J10 J11 J12 J13 J14 J15 J16 J17,Pin header 2.54mm 1x03,PinHeader_1x03_P2.54mm_Vertical,0.060,0.84,27.72,ประมาณการ
1,U4,INA219AIDR,SOIC-8_3.9x4.9mm_P1.27mm,0.780,0.78,25.74,ค้นจากเว็บ
1,J1,CUI PJ-063AH,BarrelJack_CUI_PJ-063AH_Horizontal,0.700,0.70,23.10,ประมาณการ
1,L1,6.8uH Isat>=5A 8x8mm,L_Bourns-SRN8040_8x8.15mm,0.700,0.70,23.10,ประมาณการ
1,U2,AP63205WU-7,TSOT-23-6,0.700,0.70,23.10,ประมาณการ
2,C1 C2,4.7uF 50V X7R 1210,C_1210_3225Metric,0.300,0.60,19.80,ประมาณการ
1,U7,CH340C,SOIC-16_3.9x9.9mm_P1.27mm,0.540,0.54,17.82,ค้นจากเว็บ
1,F1,"PTC 1812 hold 3A, >=16V",Fuse_1812_4532Metric,0.450,0.45,14.85,ประมาณการ
2,SW1 SW2,CK KMR2,SW_Push_1P1T_NO_CK_KMR2,0.150,0.30,9.90,ประมาณการ
1,U9,SN74AHCT541PWR,TSSOP-20_4.4x6.5mm_P0.65mm,0.300,0.30,9.90,ประมาณการ
1,C11,470uF 10V low-ESR D8,CP_Radial_D8.0mm_P3.50mm,0.250,0.25,8.25,ประมาณการ
5,C29 C30 C15 C16 C17,22uF 10V X5R 0805,C_0805_2012Metric,0.050,0.25,8.25,ประมาณการ
1,J3,HRO TYPE-C-31-M-12,USB_C_Receptacle_HRO_TYPE-C-31-M-12,0.250,0.25,8.25,ประมาณการ
3,J18 J19 J20,Pin header 2.54mm 1x04,PinHeader_1x04_P2.54mm_Vertical,0.080,0.24,7.92,ประมาณการ
1,L2,4.7uH Isat>=3A 4x4mm,L_Bourns-SRN4018,0.200,0.20,6.60,ประมาณการ
16,C10 C14 C21 C23 C25 C26 C28 C34 C35 C36 C37 C38 C39 C40 C41 C42,100nF X7R 0603,C_0603_1608Metric,0.010,0.16,5.28,ประมาณการ
5,C18 C19 C20 C22 C27,10uF 10V X5R 0805,C_0805_2012Metric,0.030,0.15,4.95,ประมาณการ
1,U6,USBLC6-2SC6,SOT-23-6,0.150,0.15,4.95,ประมาณการ
1,D3,B340B 40V 3A,D_SMB,0.120,0.12,3.96,ประมาณการ
1,R8,10mR 1% 2W 2512,R_2512_6332Metric,0.120,0.12,3.96,ประมาณการ
1,C12,100uF 25V,CP_Elec_6.3x7.7,0.120,0.12,3.96,ประมาณการ
1,C13,10uF 25V X7R 1206,C_1206_3216Metric,0.120,0.12,3.96,ประมาณการ
1,U3,AMS1117-3.3,SOT-223-3_TabPin2,0.120,0.12,3.96,ประมาณการ
1,D1,SMBJ16A,D_SMB,0.080,0.08,2.64,ประมาณการ
1,F2,PTC 1206 hold 500mA,Fuse_1206_3216Metric,0.080,0.08,2.64,ประมาณการ
2,Q2 Q3,2N7002,SOT-23,0.030,0.06,1.98,ประมาณการ
1,D5,SS34,D_SMA,0.060,0.06,1.98,ประมาณการ
12,R14 R15 R16 R30 R31 R32 R33 R34 R40 R41 R42 R43,1k 1% 0603,R_0603_1608Metric,0.005,0.06,1.98,ประมาณการ
2,Q4 Q5,MMBT3904,SOT-23,0.030,0.06,1.98,ประมาณการ
9,R13 R19 R20 R21 R35 R36 R37 R38 R39,10k 1% 0603,R_0603_1608Metric,0.005,0.04,1.48,ประมาณการ
1,D6,SS14,D_SMA,0.040,0.04,1.32,ประมาณการ
1,J21,Pin header 2.54mm 1x02,PinHeader_1x02_P2.54mm_Vertical,0.040,0.04,1.32,ประมาณการ
1,D2,BZT52C12 12V zener,D_SOD-123,0.030,0.03,0.99,ประมาณการ
1,D4,BZT52C4V7 zener,D_SOD-123,0.030,0.03,0.99,ประมาณการ
5,R24 R25 R26 R27 R28,220 1% 0603,R_0603_1608Metric,0.005,0.03,0.83,ประมาณการ
4,R1 R9 R10 R11,100k 1% 0603,R_0603_1608Metric,0.005,0.02,0.66,ประมาณการ
1,FB1,600R@100MHz 0805,L_0805_2012Metric,0.020,0.02,0.66,ประมาณการ
1,D7,LED 0603 blue,LED_0603_1608Metric,0.020,0.02,0.66,ประมาณการ
1,D8,LED 0603 green,LED_0603_1608Metric,0.020,0.02,0.66,ประมาณการ
1,D9,LED 0603 red,LED_0603_1608Metric,0.020,0.02,0.66,ประมาณการ
1,C4,100nF 16V X7R 0603,C_0603_1608Metric,0.010,0.01,0.33,ประมาณการ
1,C5,4.7nF X7R 0603,C_0603_1608Metric,0.010,0.01,0.33,ประมาณการ
1,C6,47pF X7R 0603,C_0603_1608Metric,0.010,0.01,0.33,ประมาณการ
1,C24,1uF X7R 0603,C_0603_1608Metric,0.010,0.01,0.33,ประมาณการ
2,R17 R18,5.1k 1% 0603,R_0603_1608Metric,0.005,0.01,0.33,ประมาณการ
2,R22 R23,4.7k 1% 0603,R_0603_1608Metric,0.005,0.01,0.33,ประมาณการ
1,R2,442k 1% 0603,R_0603_1608Metric,0.005,0.01,0.17,ประมาณการ
1,R3,78.7k 1% 0603,R_0603_1608Metric,0.005,0.01,0.17,ประมาณการ
1,R4,243k 1% 0603,R_0603_1608Metric,0.005,0.01,0.17,ประมาณการ
1,R5,16.9k 1% 0603,R_0603_1608Metric,0.005,0.01,0.17,ประมาณการ
1,R6,53.6k 1% 0603,R_0603_1608Metric,0.005,0.01,0.17,ประมาณการ
1,R7,10.2k 1% 0603,R_0603_1608Metric,0.005,0.01,0.17,ประมาณการ
1,R12,18k 1% 0603,R_0603_1608Metric,0.005,0.01,0.17,ประมาณการ
,,รวมอุปกรณ์ 1 บอร์ด,,,21.43,707.35,
